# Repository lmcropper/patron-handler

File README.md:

# patron-handler

Alpha Version - ESPNow

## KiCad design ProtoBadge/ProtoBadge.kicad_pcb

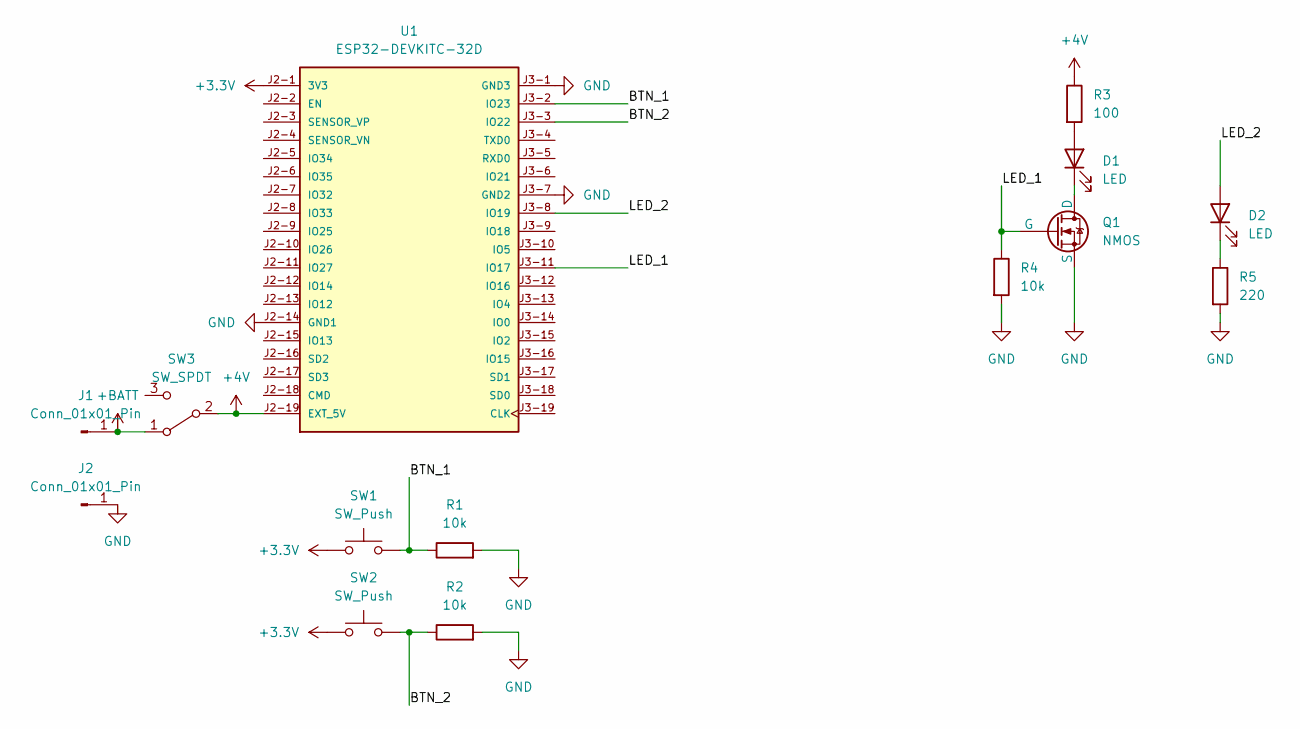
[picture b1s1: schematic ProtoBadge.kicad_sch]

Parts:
D1: LED; LED_D5.0mm_Horizontal_O3.81mm_Z3.0mm
D2: LED; LED_D3.0mm_Horizontal_O3.81mm_Z6.0mm
J1, J2: Conn_01x01_Pin; SolderWire-0.5sqmm_1x01_D0.9mm_OD2.3mm
Q1: NMOS; TO-92_Inline_Wide
R1, R2, R4: 10k; R_Axial_DIN0207_L6.3mm_D2.5mm_P10.16mm_Horizontal
R3: 100; R_Axial_DIN0207_L6.3mm_D2.5mm_P10.16mm_Horizontal
R5: 220; R_Axial_DIN0207_L6.3mm_D2.5mm_P10.16mm_Horizontal
SW1, SW2: SW_Push; SW_Push_2Prong_Horizontal
SW3: SW_SPDT; SW_SPDT_Horizontal
U1: ESP32-DEVKITC-32D; MODULE_ESP32-DEVKITC-32D; PARTREV V4

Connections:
+3.3V: SW1.1, SW2.1, U1.J2-1 (3V3)
+4V: R3.1, SW3.2 (B), U1.J2-19 (EXT_5V)
+BATT: J1.1, SW3.1 (A)
/BTN_1: R1.1, SW1.2, U1.J3-2 (IO23)
/BTN_2: R2.1, SW2.2, U1.J3-3 (IO22)
/LED_1: Q1.2 (G), R4.1, U1.J3-11 (IO17)
/LED_2: D2.2 (A), U1.J3-8 (IO19)
GND: J2.1, Q1.1 (S), R1.2, R2.2, R4.2, R5.2, U1.J2-14 (GND1), U1.J3-1 (GND3), U1.J3-7 (GND2)
unnamed: D1.2 (A), R3.2
unnamed: D1.1 (K), Q1.3 (D)
unnamed: D2.1 (K), R5.1

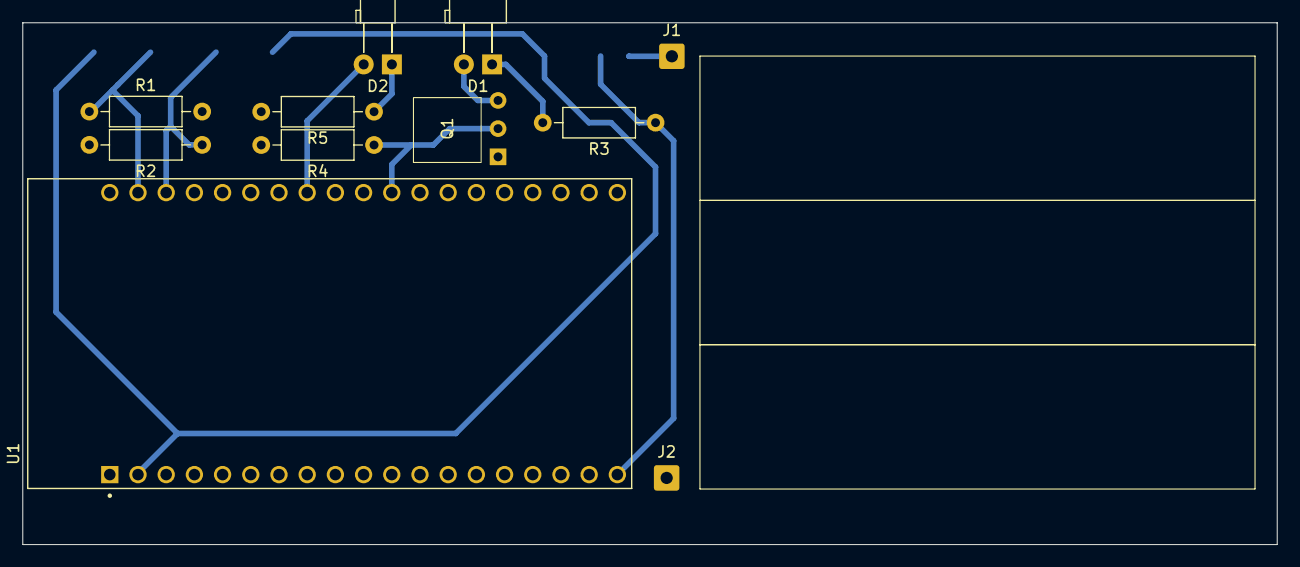
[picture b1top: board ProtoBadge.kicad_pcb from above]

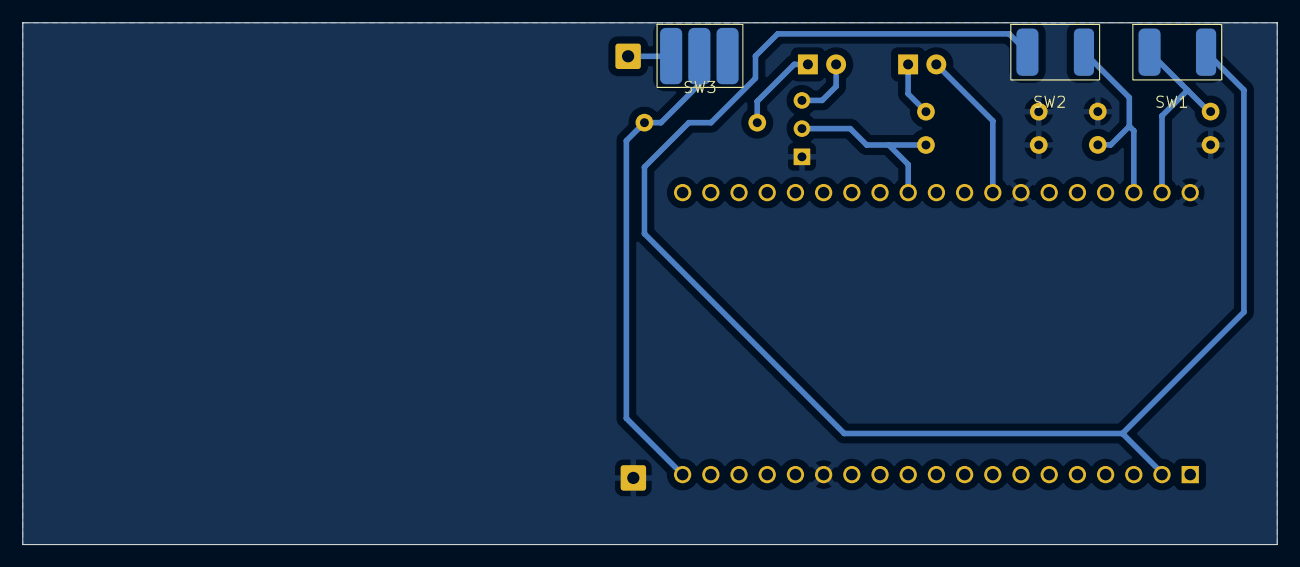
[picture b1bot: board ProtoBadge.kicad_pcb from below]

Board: 2 copper layers, 113.0 x 47.0 mm, 14 parts (3 on the bottom side), 11 nets.

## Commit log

2024-03-25 ESPNow Working Code
2024-04-19 Responds to front end communication
2024-04-19 Processing Sketch Upload
2024-04-26 Check for Inactivity
2024-04-26 Image for Inactivity Indication
2024-04-26 New Pinouts for ProtoBadge on PCB
2024-04-26 Added the Modified Button Library
2024-04-26 Reorganized Drive
2024-04-26 Added KiCad Files
2024-05-15 Minimum Viable Product implementation of MQTT com
2024-05-15 File cleanup
2024-06-21 Working on getting LCD working
